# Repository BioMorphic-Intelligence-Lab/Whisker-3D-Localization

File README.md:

# Whisker-3D-Localization

# Table of contents
1. [Overview](#overview)
2. [PCB design](#design)
3. [Data reading](#reading)
4. [3D-Localization](#3D-Localization)
   1. [Architecture](#Architecture)
   2. [Installation](#Installation)
   3. [Dataset](#Dataset)
   4. [Model training](#training) 
   5. [Test](#Test)
5. [Contact](#Contact)

## Overview 
**This repository contains open-source files for paper:**

<b>A Biomorphic Whisker Sensor for Aerial Tactile Applications</b>, Chaoxiang Ye, Guido de Croon, and Salua Hamaza. <br>
2024 IEEE International Conference on Robotics and Automation (ICRA 2024). <br>

## PCB design 

Including KiCAD files and the manufacturer's files. The manufacturer's files encompass the gerber file, Bill of Materials (BOM), and position file. The primary electronic components consist of barometers and microcontrollers. To optimize sensing ability and PCB size, we recommend utilizing the BMP390 along with the STM32F070F6. In the event of a microcontroller substitution, we recommend choosing for one with a minimum of 32Kbytes flash memory.
## Data reading 

Including all programs utilizing the STM32 to read data from three BMP390s. The SPI bus is employed for communication between the STM32 and the BMP390, where the chip select pins are sequentially lowered to read sensor data in sequence. Additionally, a UART is utilized for communication between the STM32 and the PC.

We use the In-system programming (ISP) to download the program into the STM32. Initially, the BOOT0 pin necessitates a pull-up, which entails soldering an additional wire on the PCB, connecting BOOT0 to any of the leads linked to the 3.3V (PWR-layer). Subsequently, employ the MCU ISP software to flash the "whiskeropt2.0.hex" file from the Data Reading folder onto the STM32, ensuring the baud rate is set to 115200. Please be aware that when reading data, it is imperative to configure the baud rate in accordance with the parameter specified in the "usart.c" file. In this instance, we have set it to 230400.
## 3D-Localization 
### Architecture 

### Installation 
We suggest to create a conda env
```
conda create -n whisker python=3.8
```
Clone the source code from our github repository
```
git clone https://github.com/BioMorphic-Intelligence-Lab/Whisker-3D-Localization.git
cd Whisker-3D-Localization
```

We implemented this code, under the following packages:
* Python 3.8.17
* Pytorch 2.0.1
* Numpy 1.24.3
* Scikit-learn 1.2.2

using conda to install the above packages.

Scikit-learn is exclusively utilized for selecting hyperparameters in the grid search process.

### Dataset 
The dataset was split into training, validation, and test sets. The training set contains 6,068,046 frames, while both the validation and test sets have 1,504,834 frames each. The validation set is solely employed for hyperparameter selection. We show the training dataset as an example:

### Model training 
The training set was randomly shuffled in each epoch. All models were using the Adam optimizer.
Below, we provide our optimal hyperparameters determined through the grid search method:

To train the model by our optimal hyper-parameters
```
python main.py
```

To train the model by grid search method to find the optimal hyper-parameters
```
python main.py --time_sequence [your_setting] --batch_sizes [your_setting] --learning_rates [your_setting] --regularization_values [your_setting] --dropout_values [your_setting]
```
### Test 
```
python main.py -test --model_file your_file_name
```

We also provide our model weights at [best_model_save/best_model_ts_40_bs_32_lr_0.0001_reg_0_do_0.0_loss_0.1170.pt](best_model_save/best_model_ts_40_bs_32_lr_0.0001_reg_0_do_0.0_loss_0.1170.pt)

To evaluate by our model weights
```
python main.py -test --model_file best_model_ts_40_bs_32_lr_0.0001_reg_0_do_0.0_loss_0.1170.pt
```
## Contact 
If you have any questions, feel free to contact us through email (C.Ye@tudelft.nl). Enjoy!

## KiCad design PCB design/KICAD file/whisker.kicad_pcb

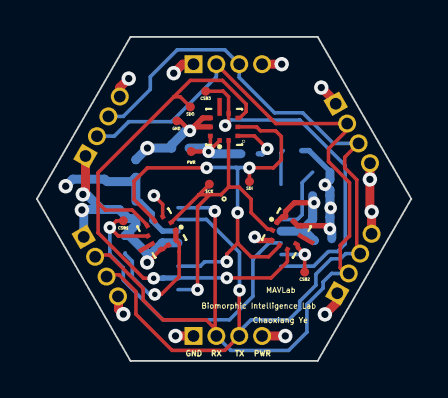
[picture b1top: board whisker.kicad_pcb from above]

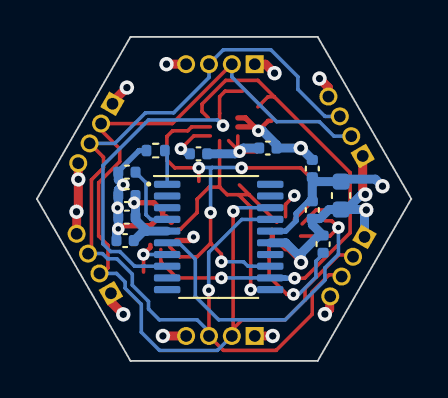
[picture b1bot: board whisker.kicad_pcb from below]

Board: 4 copper layers, 20.8 x 18.0 mm, 29 parts (17 on the bottom side), 12 nets.

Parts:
C3: 10uF; C_0603_1608Metric
C4, C5, C6, C7, C8, C9, C10, C11, C12: 100nF; C_0402_1005Metric
CSB1, CSB2, CSB3: TestPoint; TestPoint_Pad_D1.0mm
GND: TestPoint; TestPoint_Pad_D1.0mm
J1, J2, J3, J4, J5, J6: Conn_01x04_Male; PinHeader_1x04_P1.27mm_Horizontal
PWR: TestPoint; TestPoint_Pad_D1.0mm
R2: 10K; R_0402_1005Metric
SCK: TestPoint; TestPoint_Pad_D1.0mm
SDI: TestPoint; TestPoint_Pad_D1.0mm
SDO: TestPoint; TestPoint_Pad_D1.0mm
U2: STM32F070F6Px; TSSOP-20_4.4x6.5mm_P0.65mm
U3_1, U3_2, U3_3: BMP390; XDCR_BMP390L

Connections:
+3.3V: C3.1, C4.1, C5.1, C7.1, C8.1, C9.1, C10.1, C11.1, C12.1, J1.4, J2.4, J3.4, J4.4, J5.4, J6.4, PWR.1, U2.5 (VDDA), U2.16 (VDD), U3_1.1 (VDDIO), U3_1.10 (VDD), U3_2.1 (VDDIO), U3_2.10 (VDD), U3_3.1 (VDDIO), U3_3.10 (VDD)
/BOOT0: R2.2, U2.1 (BOOT0)
/CSB_1: CSB1.1, U2.6 (PA0), U3_1.6 (CSB)
/CSB_2: CSB2.1, U2.7 (PA1), U3_2.6 (CSB)
/CSB_3: CSB3.1, U2.8 (PA2), U3_3.6 (CSB)
/NRST: C6.1, U2.4 (NRST)
/RX: J1.2, J2.2, J3.2, J4.2, J5.2, J6.2, U2.18 (PA10/PA12)
/SCK: SCK.1, U2.11 (PA5), U3_1.2 (SCK), U3_2.2 (SCK), U3_3.2 (SCK)
/SDI: SDI.1, U2.13 (PA7), U3_1.4 (SDI), U3_2.4 (SDI), U3_3.4 (SDI)
/SDO: SDO.1, U2.12 (PA6), U3_1.5 (SDO), U3_2.5 (SDO), U3_3.5 (SDO)
/TX: J1.3, J2.3, J3.3, J4.3, J5.3, J6.3, U2.17 (PA9/PA11)
GND: C3.2, C4.2, C5.2, C6.2, C7.2, C8.2, C9.2, C10.2, C11.2, C12.2, GND.1, J1.1, J2.1, J3.1, J4.1, J5.1, J6.1, R2.1, U2.15 (VSS), U3_1.3 (VSS), U3_1.8 (VSS), U3_1.9 (VSS), U3_2.3 (VSS), U3_2.8 (VSS), U3_2.9 (VSS), U3_3.3 (VSS), U3_3.8 (VSS), U3_3.9 (VSS)

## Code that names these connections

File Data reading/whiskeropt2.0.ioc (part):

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Mcu.Name=STM32F070F6Px
Mcu.Package=TSSOP20
Mcu.UserName=STM32F070F6Px
PA0.GPIOParameters=PinState,GPIO_PuPd,GPIO_Label
PA0.GPIO_Label=SPI_CS1
PA0.GPIO_PuPd=GPIO_PULLUP
PA0.PinState=GPIO_PIN_SET
PA0.Signal=GPIO_Output
PA1.GPIOParameters=PinState,GPIO_PuPd,GPIO_Label
PA1.GPIO_Label=SPI_CS2
PA1.GPIO_PuPd=GPIO_PULLUP
PA1.PinState=GPIO_PIN_SET
PA1.Signal=GPIO_Output
PA10.Mode=Asynchronous
PA10.Signal=USART1_RX
PA2.GPIOParameters=PinState,GPIO_PuPd,GPIO_Label
PA2.GPIO_Label=SPI_CS3
PA2.GPIO_PuPd=GPIO_PULLUP
PA2.PinState=GPIO_PIN_SET
PA2.Signal=GPIO_Output
PA5.Mode=Full_Duplex_Master
PA5.Signal=SPI1_SCK
PA6.Mode=Full_Duplex_Master
PA6.Signal=SPI1_MISO
PA7.Mode=Full_Duplex_Master
PA7.Signal=SPI1_MOSI
PA9.Mode=Asynchronous
PA9.Signal=USART1_TX
RCC.SYSCLKFreq_VALUE=16000000
RCC.SYSCLKSource=RCC_SYSCLKSOURCE_PLLCLK
board=custom

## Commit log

2023-09-19 PCB design
2023-09-19 Data reading
2023-10-20 commit README.md
2023-10-24 images
2024-01-29 update dataset
2024-05-08 Update hyper-parameters
2024-05-08 update trainingset
2024-05-08 update hyperparameters
2024-05-12 update train,py
2024-05-12 update utils,py
2024-05-13 update learning-based localization
